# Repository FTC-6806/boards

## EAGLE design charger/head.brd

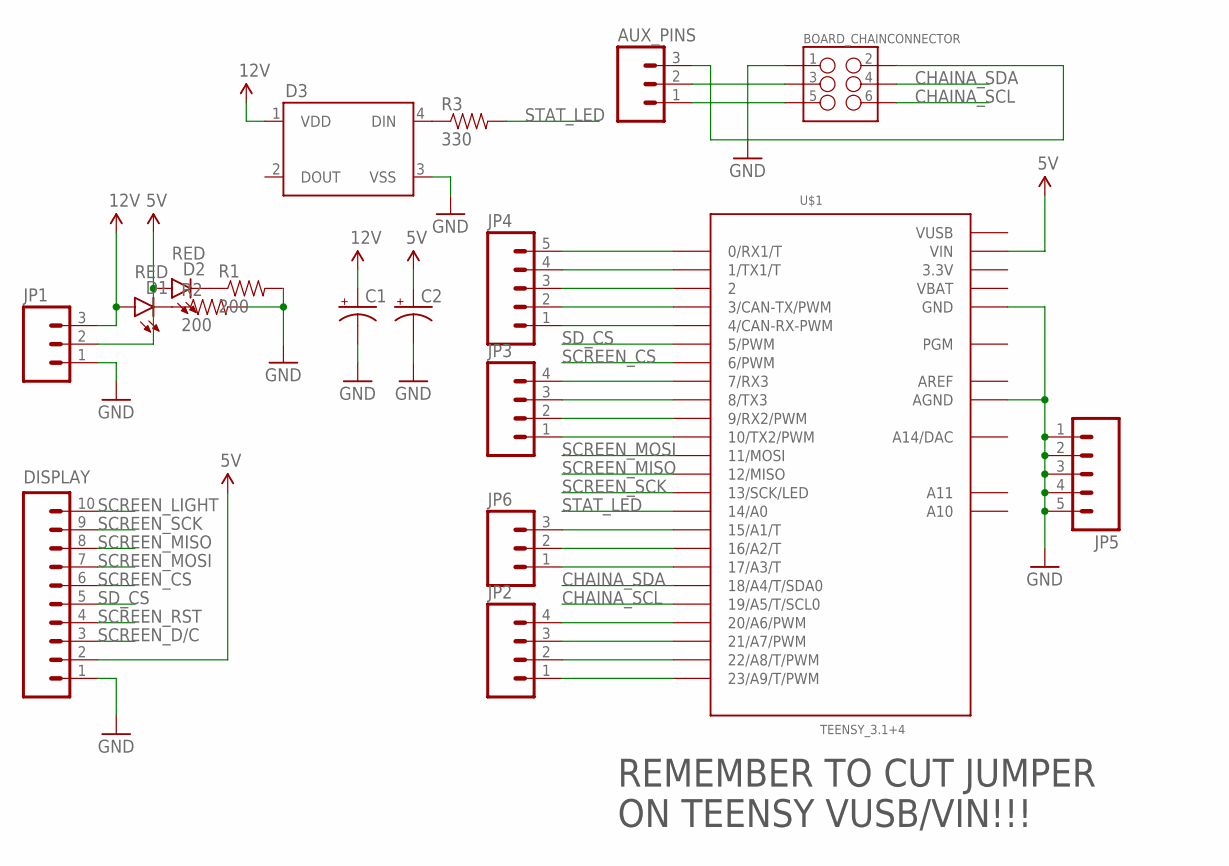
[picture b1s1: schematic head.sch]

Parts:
AUX_PINS: M03PTH; 1X03
BOARD_CHAINCONNECTOR: M03X22X3_SILK_MALE_PTH; 2X3
C1, C2: 100UF-25V-20%(PTH); CPOL-RADIAL-100UF-25V
D1, D2: RED; LED-1206
D3: WS2812B
DISPLAY: M10NO_SILK_PTH_FEMALE; 1X10_NO_SILK
JP1: M03-SCREW-5MM; SCREWTERMINAL-5MM-3
JP2, JP3: M04PTH; 1X04
JP4, JP5: M05PTH; 1X05
JP6: M03PTH; 1X03
R1, R2: 200; 0603-RES
R3: 330; AXIAL-0.1EZ
U$1: TEENSY_3.1+4

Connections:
3.3V: U$1.3.3V, U$1.3.3V1 (3.3V)
5V: C2.1 (+), D2.A, DISPLAY.2, JP1.2, U$1.VIN
12V: C1.1 (+), D1.A, D3.1 (VDD), JP1.3
AREF: U$1.AREF
CHAINA_SCL: BOARD_CHAINCONNECTOR.6, U$1.19/A5 (19/A5/T/SCL0)
CHAINA_SDA: BOARD_CHAINCONNECTOR.4, U$1.18/A4 (18/A4/T/SDA0)
GND: BOARD_CHAINCONNECTOR.1, C1.2 (-), C2.2 (-), D3.3 (VSS), DISPLAY.1, JP1.1, JP5.1, JP5.2, JP5.3, JP5.4, JP5.5, R1.2, R2.2, U$1.AGND, U$1.GND, U$1.GND1 (GND)
unnamed: AUX_PINS.2, BOARD_CHAINCONNECTOR.3
unnamed: AUX_PINS.1, BOARD_CHAINCONNECTOR.5
unnamed: AUX_PINS.3, BOARD_CHAINCONNECTOR.2
unnamed: D2.C, R1.1
unnamed: D1.C, R2.1
unnamed: D3.4 (DIN), R3.P$1 (1)
unnamed: JP6.3, U$1.15/A1 (15/A1/T)
unnamed: JP2.4, U$1.20/A6 (20/A6/PWM)
unnamed: JP2.3, U$1.21/A7 (21/A7/PWM)
unnamed: JP2.2, U$1.22/A8 (22/A8/T/PWM)
unnamed: JP2.1, U$1.23/A9 (23/A9/T/PWM)
unnamed: JP3.1, U$1.10 (10/TX2/PWM)
unnamed: JP3.2, U$1.9 (9/RX2/PWM)
unnamed: JP3.3, U$1.8 (8/TX3)
unnamed: JP3.4, U$1.7 (7/RX3)
unnamed: JP4.1, U$1.4 (4/CAN-RX-PWM)
unnamed: JP4.2, U$1.3 (3/CAN-TX/PWM)
unnamed: JP4.3, U$1.2
unnamed: JP4.4, U$1.1 (1/TX1/T)
unnamed: JP4.5, U$1.0 (0/RX1/T)
unnamed: JP6.2, U$1.16/A2 (16/A2/T)
unnamed: JP6.1, U$1.17/A3 (17/A3/T)
SCREEN_CS: DISPLAY.6, U$1.6 (6/PWM)
SCREEN_D/C: DISPLAY.3
SCREEN_LIGHT: DISPLAY.10
SCREEN_MISO: DISPLAY.8, U$1.12 (12/MISO)
SCREEN_MOSI: DISPLAY.7, U$1.11 (11/MOSI)
SCREEN_RST: DISPLAY.4
SCREEN_SCK: DISPLAY.9, U$1.13 (13/SCK/LED)
SD_CS: DISPLAY.5, U$1.5 (5/PWM)
STAT_LED: R3.P$2 (2), U$1.14/A0
VBAT: U$1.VBAT
VUSB: U$1.VUSB

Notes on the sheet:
REMEMBER TO CUT JUMPER ON TEENSY VUSB/VIN!!!

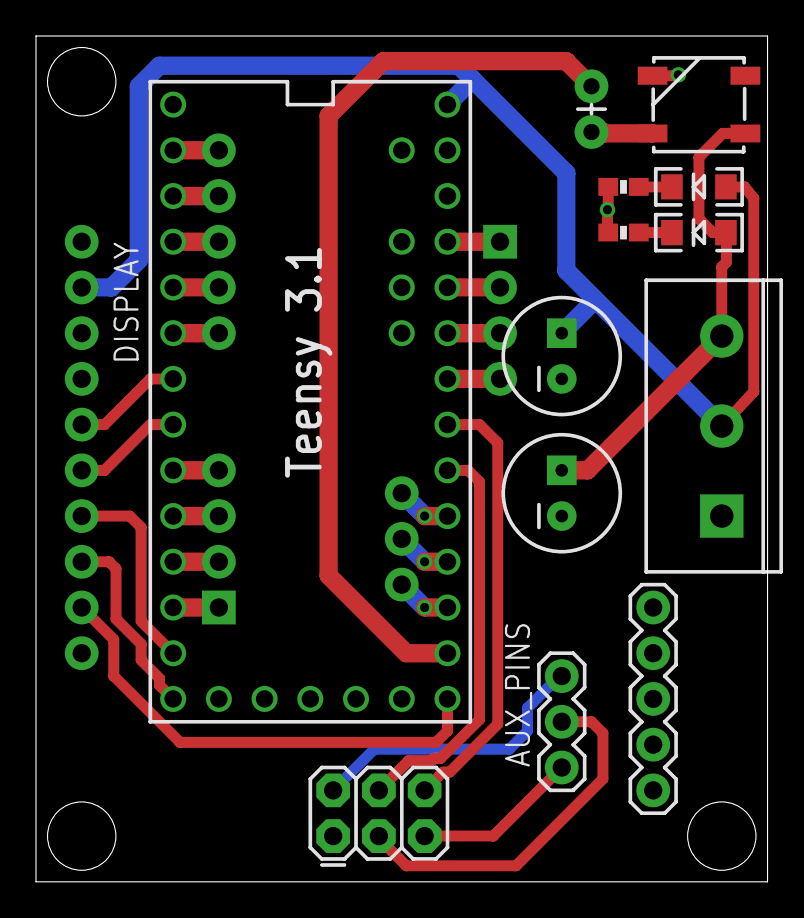
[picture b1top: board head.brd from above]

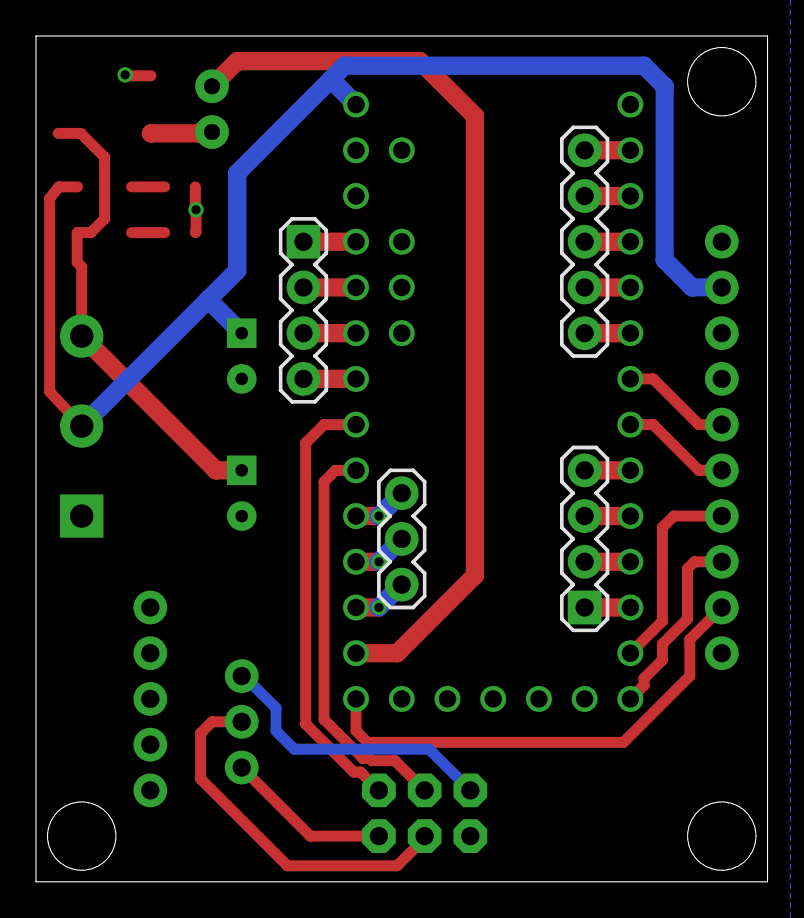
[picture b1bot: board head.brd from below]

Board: 2 copper layers, 40.6 x 47.0 mm, 18 parts (4 on the bottom side), 34 nets.

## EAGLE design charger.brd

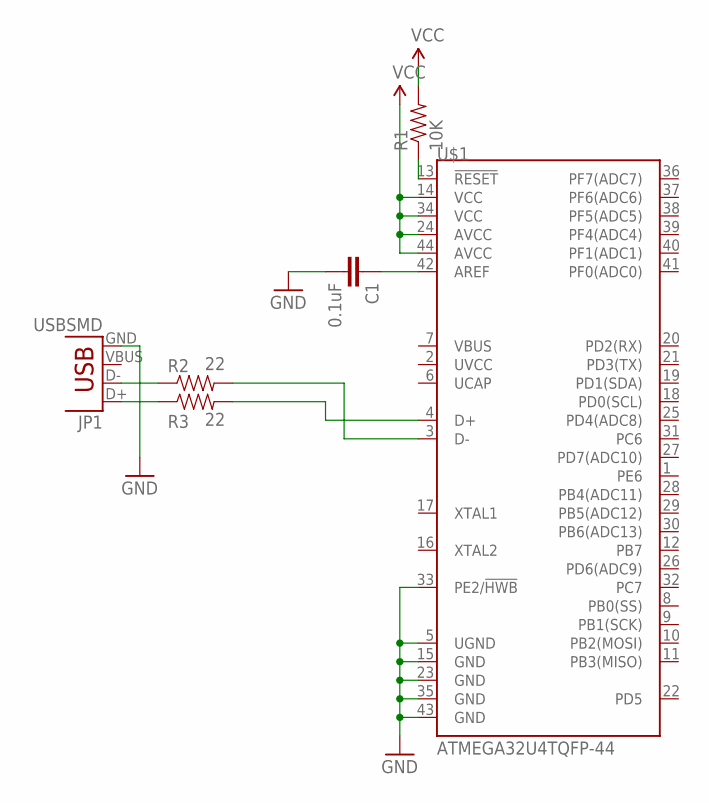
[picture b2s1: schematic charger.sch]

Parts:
C1: 0.1uF; 0603-CAP
JP1: USBSMD; USB-MINIB
R1: 10K; 0603-RES
R2, R3: 22; 0603-RES
U$1: ATMEGA32U4TQFP-44; TQFP44

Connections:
GND: C1.2, JP1.GND, U$1.5 (UGND), U$1.15 (GND), U$1.23 (GND), U$1.33 (PE2/!HWB), U$1.35 (GND), U$1.43 (GND)
unnamed: R1.1, U$1.13 (!RESET)
unnamed: C1.1, U$1.42 (AREF)
unnamed: JP1.D-, R2.1
unnamed: JP1.D+, R3.1
unnamed: R2.2, U$1.3 (D-)
unnamed: R3.2, U$1.4 (D+)
VCC: R1.2, U$1.14 (VCC), U$1.24 (AVCC), U$1.34 (VCC), U$1.44 (AVCC)

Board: 2 copper layers, 6 parts (0 on the bottom side), 8 nets, no tracks yet.

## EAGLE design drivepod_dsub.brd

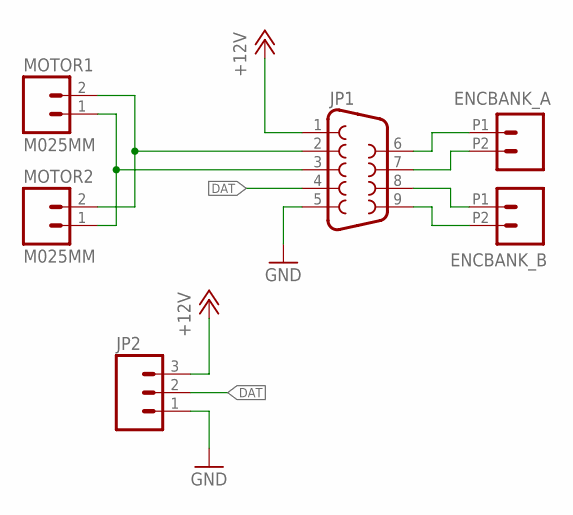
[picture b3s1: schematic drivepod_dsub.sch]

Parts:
ENCBANK_A: M022.54MM_SCREWTERM; 1X02_2.54_SCREWTERM
ENCBANK_B: M022.54MM_SCREWTERM; 1X02_2.54_SCREWTERM
JP1: DB9MALE; DB9_MALE
JP2: M03SCREW; SCREWTERMINAL-3.5MM-3
MOTOR1, MOTOR2: M025MM; SCREWTERMINAL-5MM-2

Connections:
+12V: JP1.1, JP2.3
DAT: JP1.4, JP2.2
GND: JP1.5, JP2.1
unnamed: JP1.2, MOTOR1.2, MOTOR2.2
unnamed: JP1.3, MOTOR1.1, MOTOR2.1
unnamed: ENCBANK_B.P1 (1), JP1.8
unnamed: ENCBANK_B.P2 (2), JP1.9
unnamed: ENCBANK_A.P1 (1), JP1.6
unnamed: ENCBANK_A.P2 (2), JP1.7

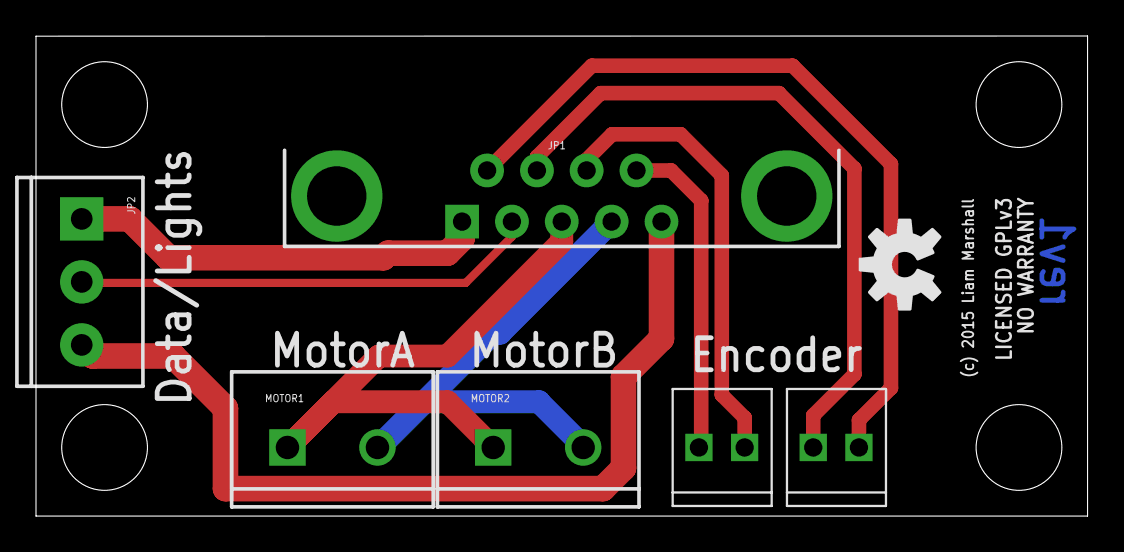
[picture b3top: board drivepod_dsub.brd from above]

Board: 2 copper layers, 58.4 x 26.7 mm, 7 parts (0 on the bottom side), 9 nets.

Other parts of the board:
U$1: OSHW-LOGO-M

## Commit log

2015-03-09 Initial commit :D
2015-03-09 Drivepod dsub
2015-03-09 Charger stuff
2015-09-21 :fire: Yank old charger files
2015-09-21 New files for the charger controller/display head
2015-10-13 Improve the design and layout of the charger head
    - smaller board
    - wire up Teensy to power
    - add ws2812 status led
    - add filtering caps
    - add mounting holes
    - downgrade to 3x2 header for interboard comms
2015-10-13 Add a few nice things to the control head
    - break out a bunch of teensy pins
    - add a resistor to the ws2812 for reliability
    - a bit of rerouting

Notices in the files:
drivepod_dsub.brd:
(c) 2015 Liam Marshall
LICENSED GPLv3
parts and their libraries:
SparkFun-DigitalIC: Licensing: Creative Commons ShareAlike 4.0 International - https://creativecommons.org/licenses/by-sa/4.0
